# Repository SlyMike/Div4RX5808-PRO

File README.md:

# Div4RX5808-PRO
Arduino based 5.8GHz  Diversity Video receiver using 2x RX5808-PRO RX modules.

This project requires that you make 3 seperate PCB's. Two RX5808-PRO enabled video RX modules and a Diversity main board.
Boards and schematics are supplied for both the receivers and mainboard. 
Boards and schematics are in Eagle PCB format.

The RX modules will need to be assembled and programmed with the RX5808-PRO software (available on Github).
The diversity code for the Main board is available within this repository. After downloading, replace the .C file extension with .ino and upload.

The Main board and RX modules will require an Arduino Nano with an Atmega328.

The software portion of this project is not an adaptation of RX5808-PRO, it's function is to monitor 2x RSSI inputs from 2x RX5808-PRO enabled receivers and display the video feed from the receiver with the better signal. 
Video, audio and controls are switched simultaniously. LEDs indicate RSSI percentage (4 LEDs), active receiver (2 LEDs) and diversity mode (1 LED).

Holding the "Video" button during boot will allow for RSSI calibration as many RX5808 modules will have slightly different lower and upper limits.
The Div4RX5808-PRO diversity video receiver will assume that channel selection is correct and that nobody else is using the chosen channel.
The transmitter on the RC model should be set to the same channel as the receiver, the model should be powered down.

(1) Turn on Div4RX5808-PRO diversity video receiver in RSSI calibration mode (TX OFF). Amber led indicates LOW RSSI calculation. Press and release "Mode" button.
(2) Turn on transmitter. Second amber led indicates HIGH RSSI calculation. Press and release "Mode" button.
(3) Green LED indicates a good calibration, red a failure.

Auto calibration may not be necessary and if it is not initiated on power up (or fails for some reason), received RSSI values will be directly compared as if limits are equal on both modules.

Hold the "Mode" button during power up to enable serial debug output.

The code has been tested to a degree, it seems to work for me but there is always room for improvement.
I consider this project a work in progress, you may find bugs, spelling mistakes, missing component values, most of the source files were made in a rush or whilst I was doing something else.

I may address this in future but for most folk it should not be hard to build.

The point of this project was to create a decent micro controlled diversity receiver with better features than some of the crude homebrew solutions that I found on the net. I'm pretty sure I met my goal!

      FEATURES:
      
      *** AUTO RSSI CALIBRATION ***
      
      RX5808-PRO SUPPORT.
      
      LIVE VIDEO / SPECTRUM ANALYSER SWITCHING VIA PUSH BUTTON.
      SINGLE RX OR DIVERSITY MODES VIA PUSH BUTTON.
      SERIAL DEBUG MODE VIA PUSH BUTTON.
      TOTAL 6 PUSH BUTTONS FOR EASY OPERATION.
      SOFTWARE SWITCH DE-BOUNCING.
      
      MODE LED INDICATORS.
      RSSI LED INDICATORS.
      RX LED INDICATORS.
      
      VARIABLE RSSI SMOOTHING.
      VARIABLE RX SWITCHING RATE.
      VARIABLE RSSI HYSTERESIS.
      
      CHOICE OF VOLTAGE REFERENCE METHODS - CODE WILL WORK ON 3V3 AND 5V TARGETS.
      WELL COMMENTED CODE.

I hope you find this project helpful, maybe it's worth a coffee?

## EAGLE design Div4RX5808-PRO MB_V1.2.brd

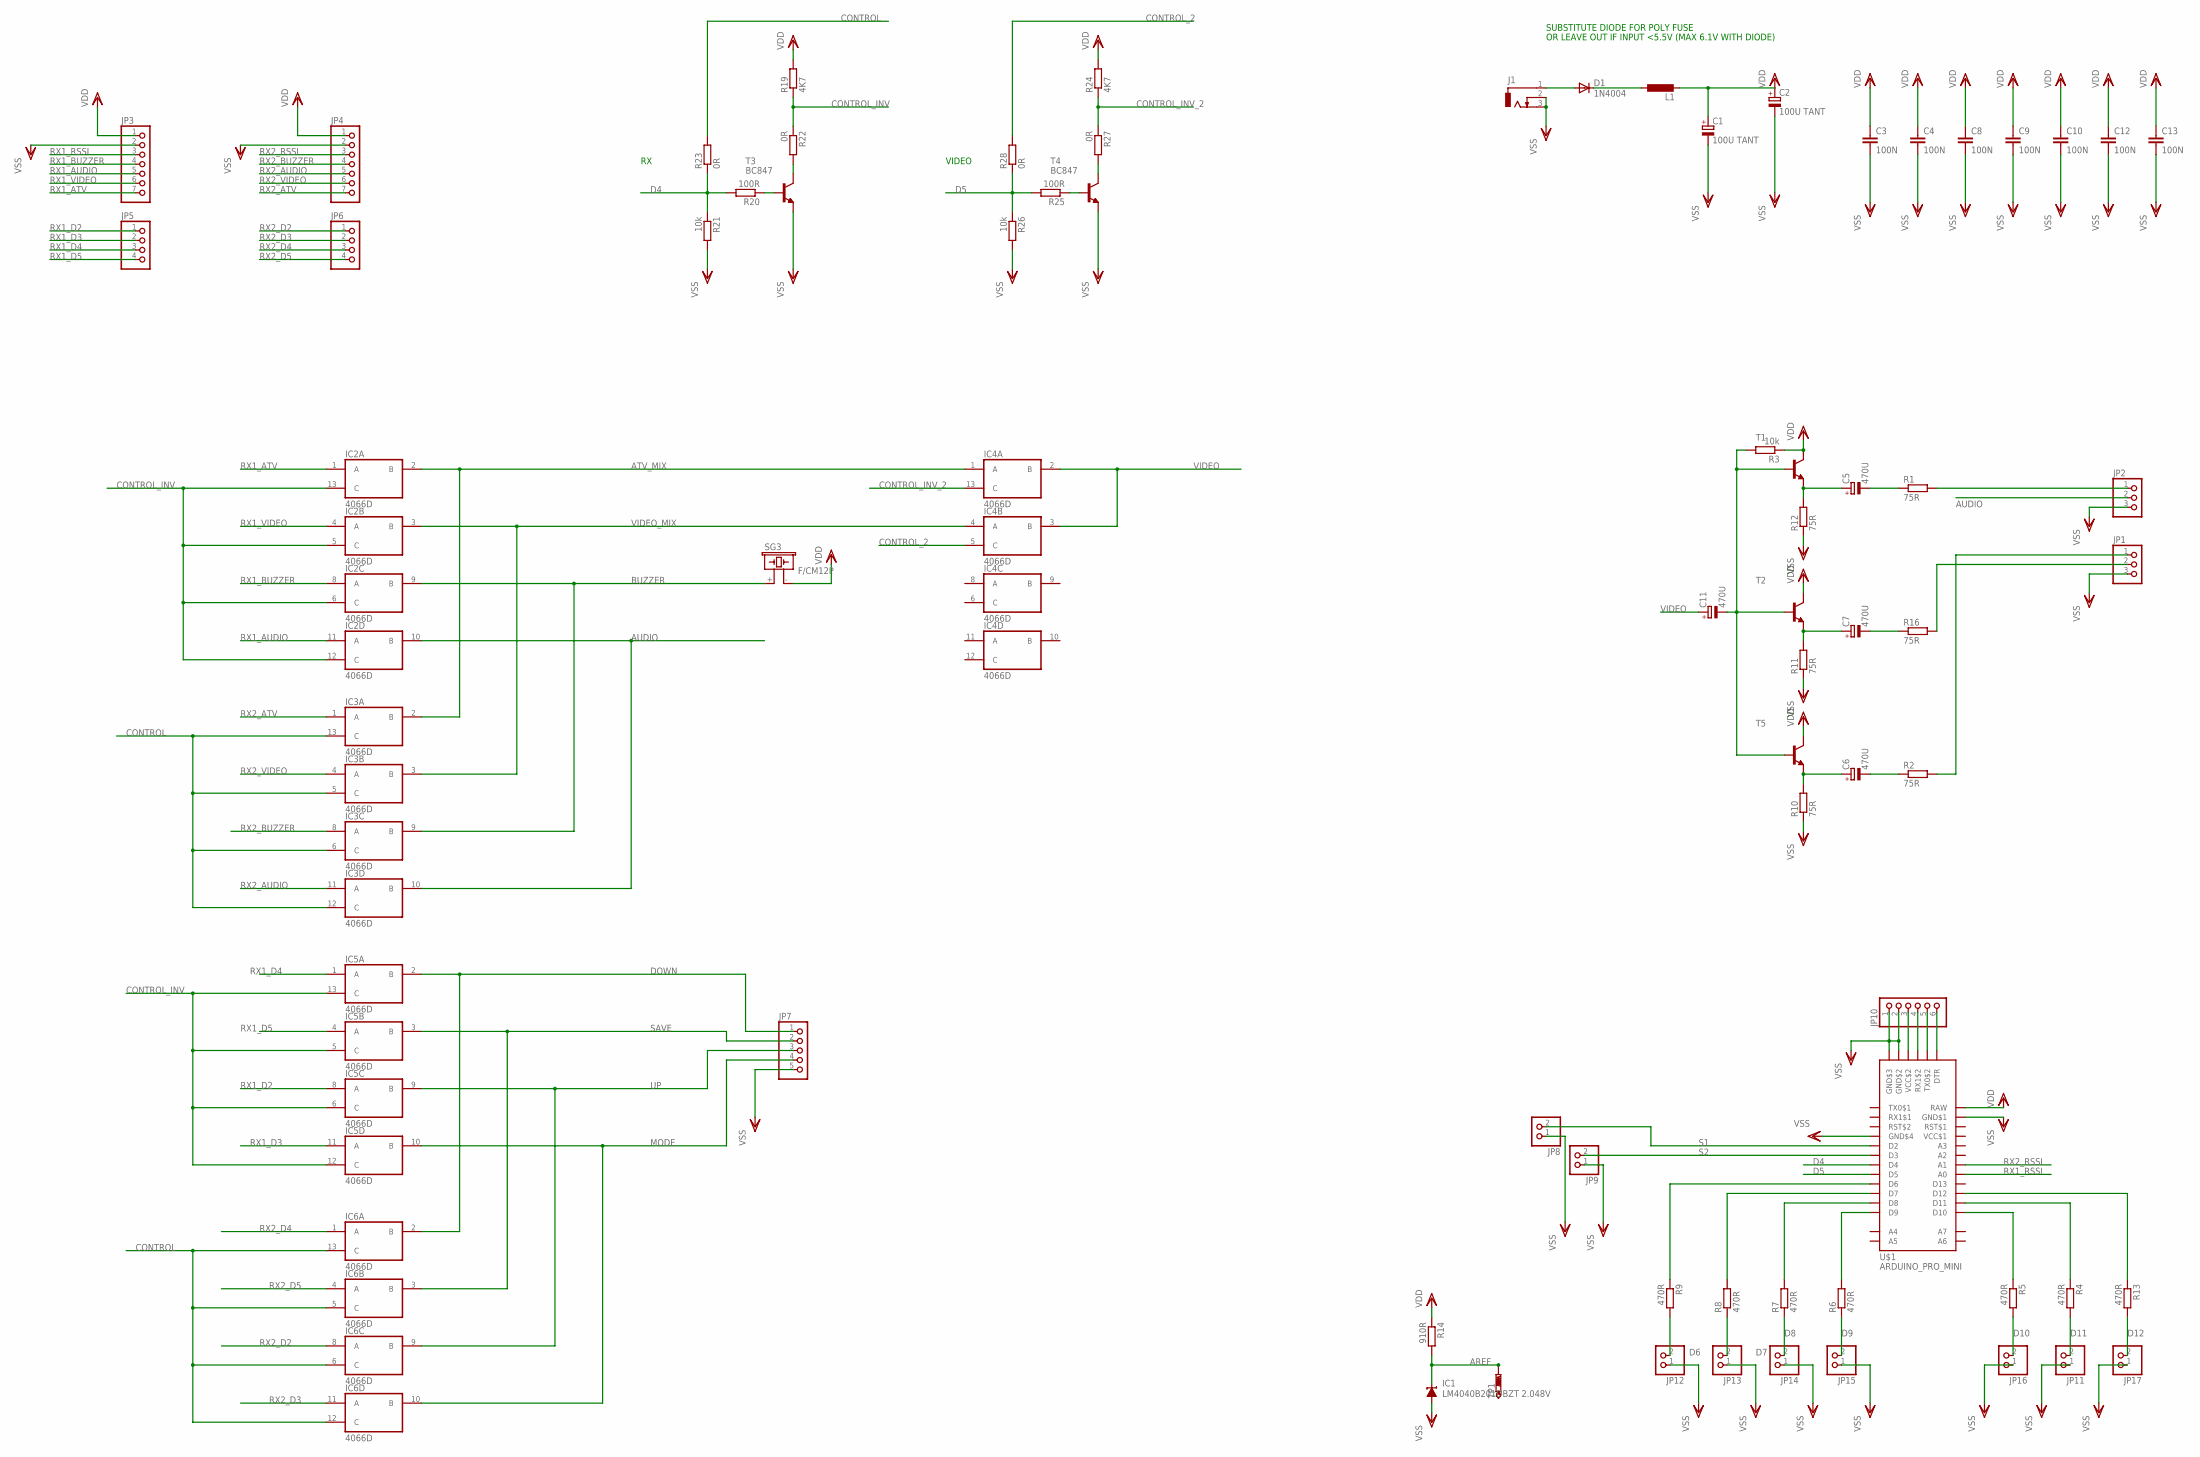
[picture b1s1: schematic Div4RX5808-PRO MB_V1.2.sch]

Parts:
C1, C2: 100U TANT; C/6032-28R
C3, C4, C8, C9, C10, C12, C13: 100N; C0603
C5, C6, C7, C11: 470U; E5-10,5
D1: 1N4004; DO41-10
IC1: LM4040B201DBZT 2.048V; DBZ_R-PDSO-G3
IC2, IC3, IC4, IC5, IC6: 4066D; SO14
J1: DCJ0303
JP1, JP2: PINHD-1X3; 1X03
JP3, JP4: PINHD-1X7; 1X07
JP5, JP6: PINHD-1X4; 1X04
JP7: PINHD-1X5; 1X05
JP8, JP9, JP11, JP12, JP13, JP14, JP15, JP16, JP17: PINHD-1X2; 1X02
JP10: PINHD-1X6; 1X06
L1: L-EU0207/7; 0207/7
R1, R2, R10, R11, R12, R16: 75R; M0805
R3, R21, R26: 10k; M0805
R4, R5, R6, R7, R8, R9, R13: 470R; R0603
R14: 910R; R0603
R19, R24: 4K7; M0805
R20, R25: 100R; M0805
R22, R23, R27, R28: 0R; M0805
SG3: F/CM12P
T1, T2, T5: MMBT2222ALT1-NPN-SOT23-BEC; SOT23-BEC
T3, T4: BC847; SOT23-BEC
TP1: PTR1TP20SQ; TP20SQ
U$1: ARDUINO_PRO_MINI

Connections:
AREF: IC1.1 (C), R14.2, TP1.TP
ATV_MIX: IC2.2 (B), IC3.2 (B), IC4.1 (A)
AUDIO: IC2.10 (B), IC3.10 (B), JP2.2
BUZZER: IC2.9 (B), IC3.9 (B), SG3.+ (1)
CONTROL: IC3.5 (C), IC3.6 (C), IC3.12 (C), IC3.13 (C), IC6.5 (C), IC6.6 (C), IC6.12 (C), IC6.13 (C), R23.2
CONTROL_2: IC4.5 (C), R28.2
CONTROL_INV: IC2.5 (C), IC2.6 (C), IC2.12 (C), IC2.13 (C), IC5.5 (C), IC5.6 (C), IC5.12 (C), IC5.13 (C), R19.1, R22.1
CONTROL_INV_2: IC4.13 (C), R24.1, R27.1
D4: R20.2, R21.1, R23.1, U$1.D4
D5: R25.2, R26.1, R28.1, U$1.D5
D6: JP12.2, R9.2
D7: JP13.2, R8.1
D8: JP14.2, R7.1
D9: JP15.2, R6.1
D10: JP16.2, R5.2
D11: JP11.2, R4.2
D12: JP17.2, R13.2
DOWN: IC5.2 (B), IC6.2 (B), JP7.1
MODE: IC5.10 (B), IC6.10 (B), JP7.4
unnamed: D1.C, L1.1
unnamed: D1.A, J1.1
unnamed: R13.1, U$1.D12
unnamed: C5.-, R1.1
unnamed: C6.-, R2.1
unnamed: JP2.1, R1.2
unnamed: C7.-, R16.1
unnamed: JP1.2, R16.2
unnamed: JP1.1, R2.2
unnamed: C5.+, R12.2, T1.E
unnamed: JP10.6, U$1.DTR
unnamed: JP10.5, U$1.TX0$2
unnamed: C7.+, R11.2, T2.E
unnamed: JP10.4, U$1.RX1$2
unnamed: JP10.3, U$1.VCC$2
unnamed: R25.1, T4.B
unnamed: C6.+, R10.2, T5.E
unnamed: R22.2, T3.C
unnamed: R20.1, T3.B
unnamed: R27.2, T4.C
unnamed: C11.-, R3.2, T1.B, T2.B, T5.B
unnamed: R9.1, U$1.D6
unnamed: R8.2, U$1.D7
unnamed: R6.2, U$1.D9
unnamed: R4.1, U$1.D11
unnamed: R5.1, U$1.D10
unnamed: R7.2, U$1.D8
RX1_ATV: IC2.1 (A), JP3.7
RX1_AUDIO: IC2.11 (A), JP3.5
RX1_BUZZER: IC2.8 (A), JP3.4
RX1_D2: IC5.8 (A), JP5.1
RX1_D3: IC5.11 (A), JP5.2
RX1_D4: IC5.1 (A), JP5.3
RX1_D5: IC5.4 (A), JP5.4
RX1_RSSI: JP3.3, U$1.A0
RX1_VIDEO: IC2.4 (A), JP3.6
RX2_ATV: IC3.1 (A), JP4.7
RX2_AUDIO: IC3.11 (A), JP4.5
RX2_BUZZER: IC3.8 (A), JP4.4
RX2_D2: IC6.8 (A), JP6.1
RX2_D3: IC6.11 (A), JP6.2
RX2_D4: IC6.1 (A), JP6.3
RX2_D5: IC6.4 (A), JP6.4
RX2_RSSI: JP4.3, U$1.A1
RX2_VIDEO: IC3.4 (A), JP4.6
S1: JP8.2, U$1.D2
S2: JP9.2, U$1.D3
SAVE: IC5.3 (B), IC6.3 (B), JP7.2
UP: IC5.9 (B), IC6.9 (B), JP7.3
VCC$1: U$1.VCC$1
VDD: C1.+, C2.+, C3.1, C4.1, C8.1, C9.1, C10.1, C12.1, C13.1, IC2.14 (VDD), IC3.14 (VDD), IC4.14 (VDD), IC5.14 (VDD), IC6.14 (VDD), JP3.1, JP4.1, L1.2, R3.1, R14.1, R19.2, R24.2, SG3.- (2), T1.C, T2.C, T5.C, U$1.RAW
VIDEO: C11.+, IC4.2 (B), IC4.3 (B)
VIDEO_MIX: IC2.3 (B), IC3.3 (B), IC4.4 (A)
VSS: C1.-, C2.-, C3.2, C4.2, C8.2, C9.2, C10.2, C12.2, C13.2, IC1.2 (A), IC2.7 (VSS), IC3.7 (VSS), IC4.7 (VSS), IC5.7 (VSS), IC6.7 (VSS), J1.2, J1.3, JP1.3, JP2.3, JP3.2, JP4.2, JP7.5, JP8.1, JP9.1, JP10.1, JP10.2, JP11.1, JP12.1, JP13.1, JP14.1, JP15.1, JP16.1, JP17.1, R10.1, R11.1, R12.1, R21.2, R26.2, T3.E, T4.E, U$1.GDN$1 (GND$1), U$1.GND$2, U$1.GND$3, U$1.GND$4

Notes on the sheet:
VIDEO
SUBSTITUTE DIODE FOR POLY FUSE
OR LEAVE OUT IF INPUT <5.5V (MAX 6.1V WITH DIODE)

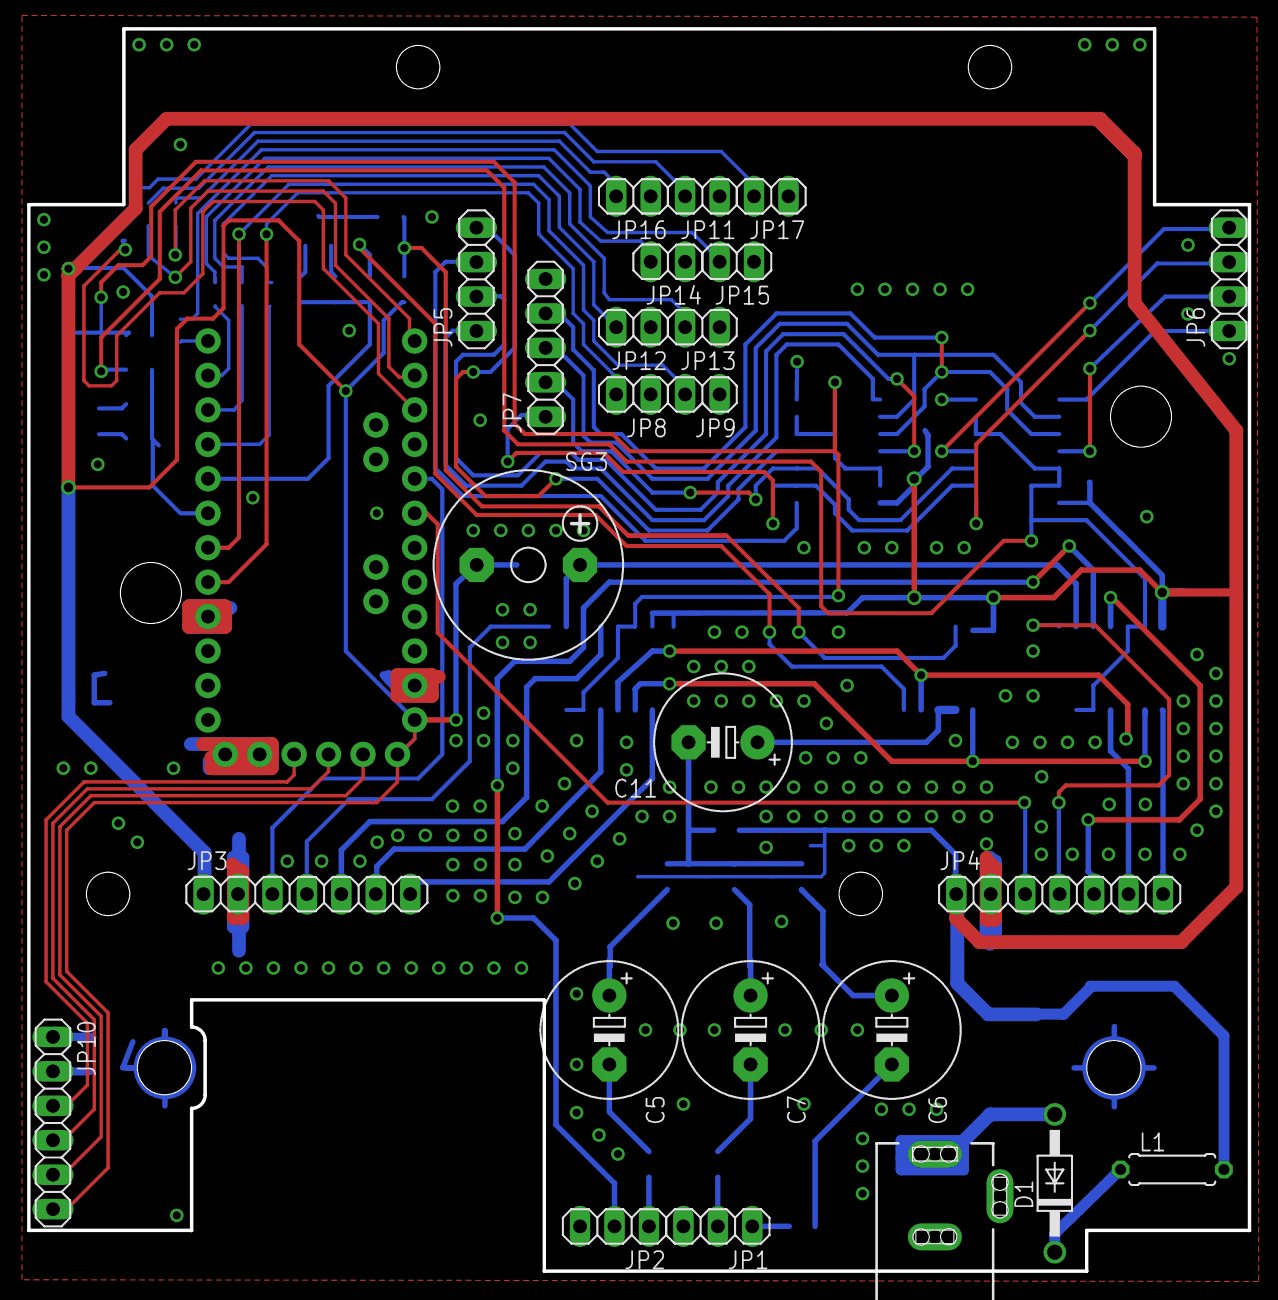
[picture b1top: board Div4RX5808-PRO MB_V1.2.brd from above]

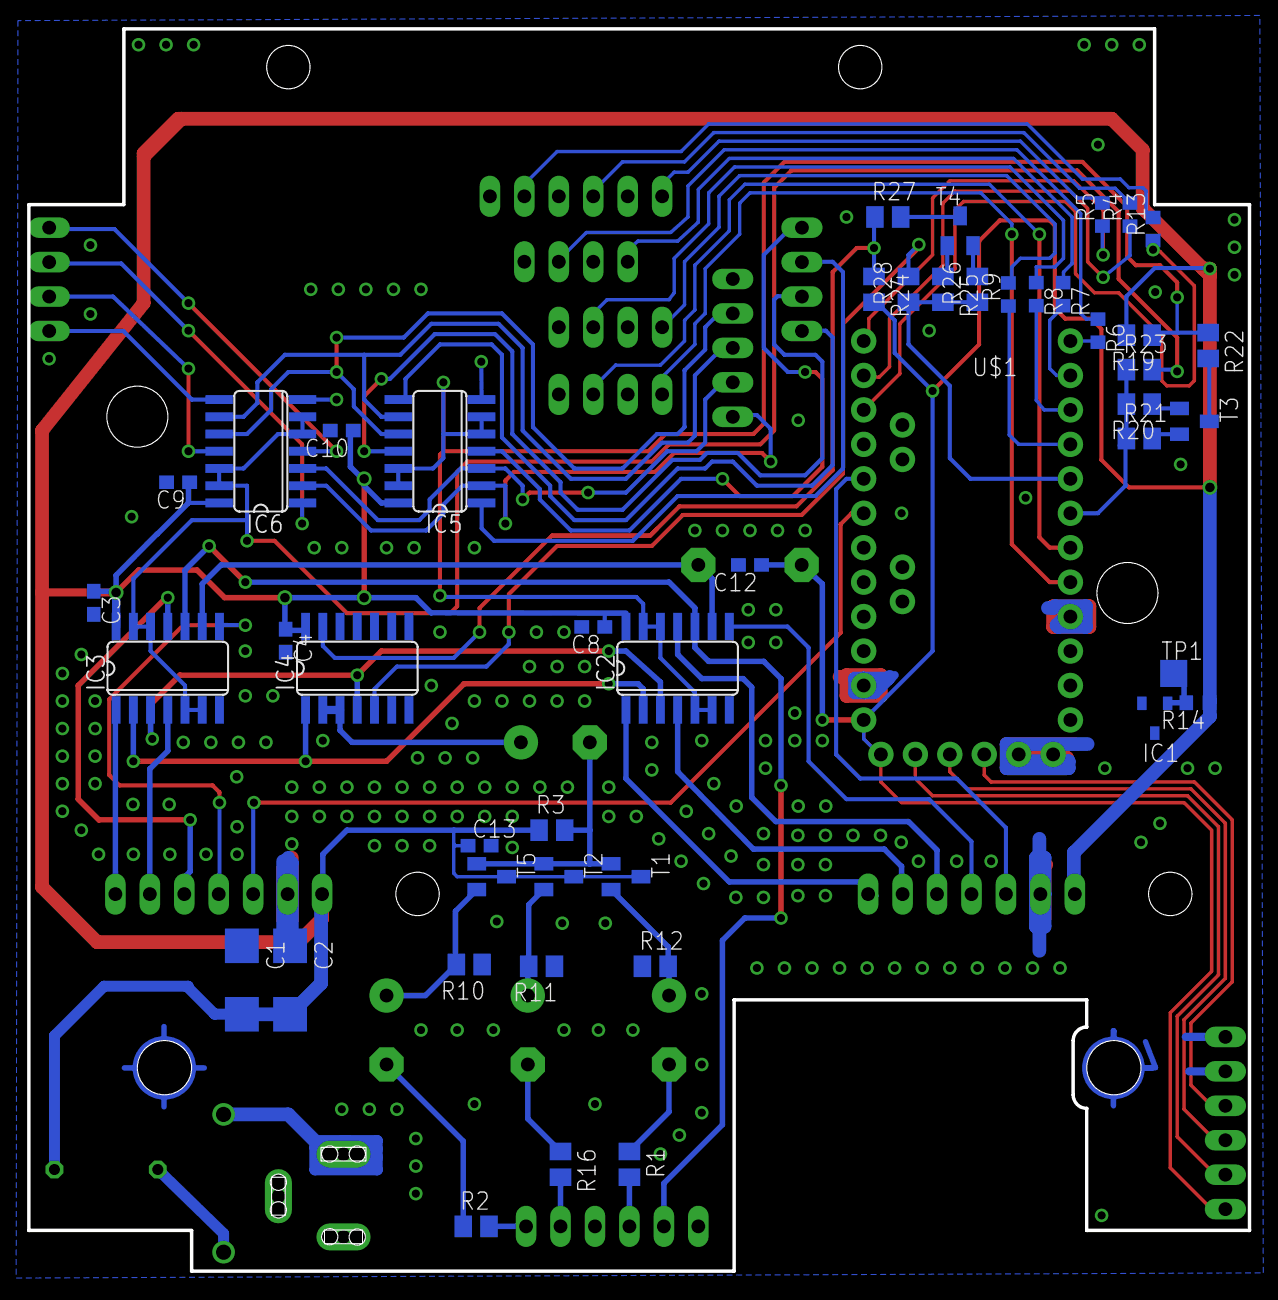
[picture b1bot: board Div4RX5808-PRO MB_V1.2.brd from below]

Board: 2 copper layers, 90.0 x 91.6 mm, 72 parts (47 on the bottom side), 72 nets.

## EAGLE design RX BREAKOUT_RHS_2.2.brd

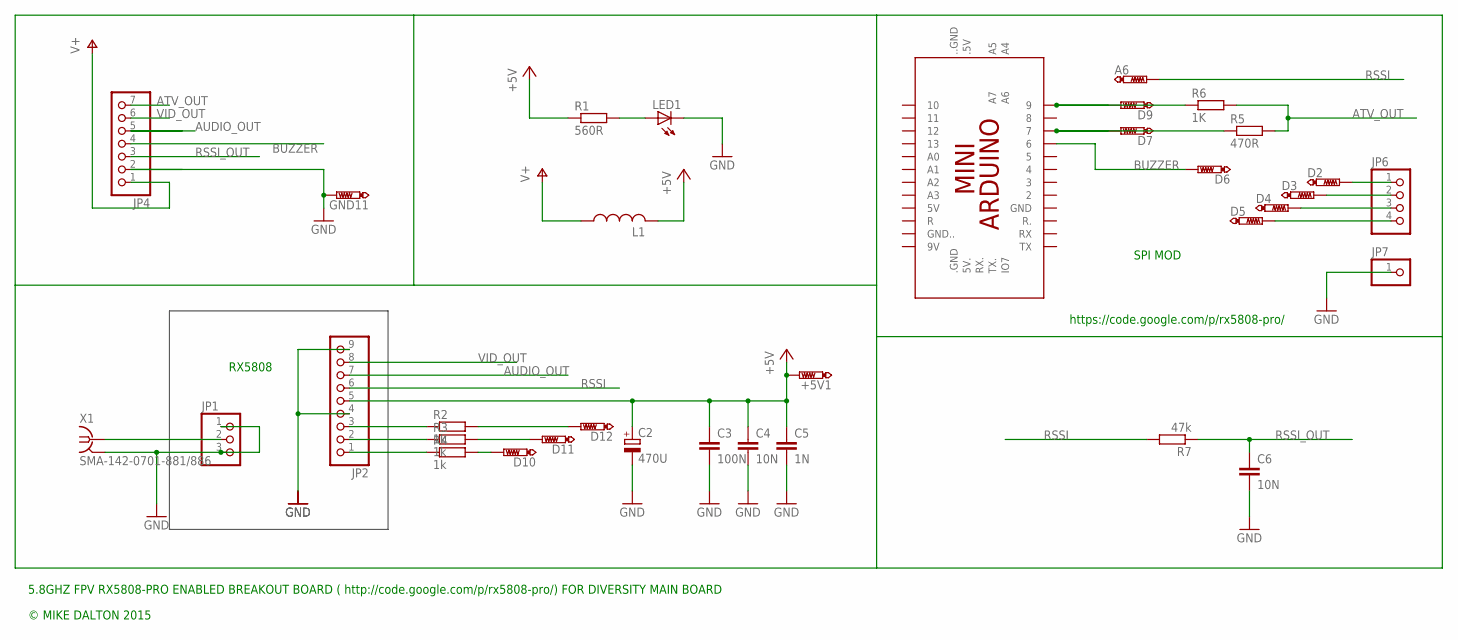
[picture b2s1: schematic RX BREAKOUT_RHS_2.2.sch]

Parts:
+5V1: PTR1TP16SQ; TP16SQ
A6: PTR1TP16SQ; TP16SQ
C2: 470U; E5-10,5
C3: 100N; C0603K
C4, C6: 10N; C0603K
C5: 1N; C0603K
D2, D3, D4, D5, D6, D7, D9, D10, D11, D12: PTR1TP16SQ; TP16SQ
GND11: PTR1TP16SQ; TP16SQ
JP1: PINHD-1X3; 1X03
JP2: PINHD-1X9; 1X09
JP4: PINHD-1X7; 1X07
JP6: PINHD-1X4; 1X04
JP7: PINHD-1X1; 1X01
L1: L-USL4532C; L4532M
LED1: LEDSMT1206; 1206
R1: 560R; R0603
R2, R3, R4: 1k; R0603
R5: 470R; R0603
R6: 1K; R0603
R7: 47k; R0603
X1: SMA-142-0701-881/886; J502-ND-142-0701-881/886

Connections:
ATV_OUT: JP4.7, R5.2, R6.2
AUDIO_OUT: JP2.7, JP4.5
BUZZER: D6.TP, JP4.4
D7: D7.TP, R5.1
D9: D9.TP, R6.1
GND: C2.-, C3.2, C4.2, C5.2, C6.2, GND11.TP, JP1.1, JP1.3, JP2.4, JP2.9, JP4.2, JP7.1, LED1.C, X1.G@1 (2), X1.G@2 (2), X1.G@3 (2), X1.G@4 (2)
unnamed: D12.TP, R2.2
unnamed: JP2.3, R2.1
unnamed: D11.TP, R3.2
unnamed: LED1.A, R1.2
unnamed: JP1.2, X1.1
unnamed: D10.TP, R4.2
unnamed: JP2.2, R3.1
unnamed: +5V1.TP, C2.+, C3.1, C4.1, C5.1, JP2.5, L1.2, R1.1
unnamed: JP2.1, R4.1
unnamed: D2.TP, JP6.1
unnamed: D3.TP, JP6.2
unnamed: D4.TP, JP6.3
unnamed: D5.TP, JP6.4
RSSI: A6.TP, JP2.6, R7.2
RSSI_OUT: C6.1, JP4.3, R7.1
V+: JP4.1, L1.1
VID_OUT: JP2.8, JP4.6

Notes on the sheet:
RX5808
SPI MOD
https://code.google.com/p/rx5808-pro/
© MIKE DALTON 2015
5.8GHZ FPV RX5808-PRO ENABLED BREAKOUT BOARD ( http://code.google.com/p/rx5808-pro/) FOR DIVERSITY MAIN BOARD

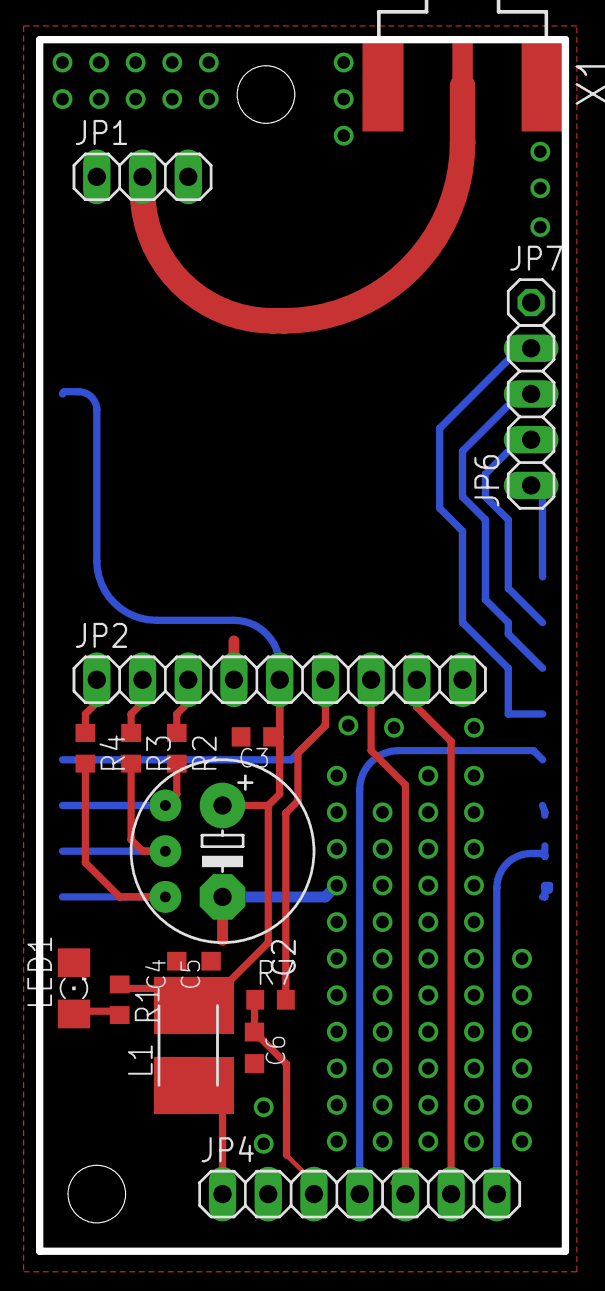
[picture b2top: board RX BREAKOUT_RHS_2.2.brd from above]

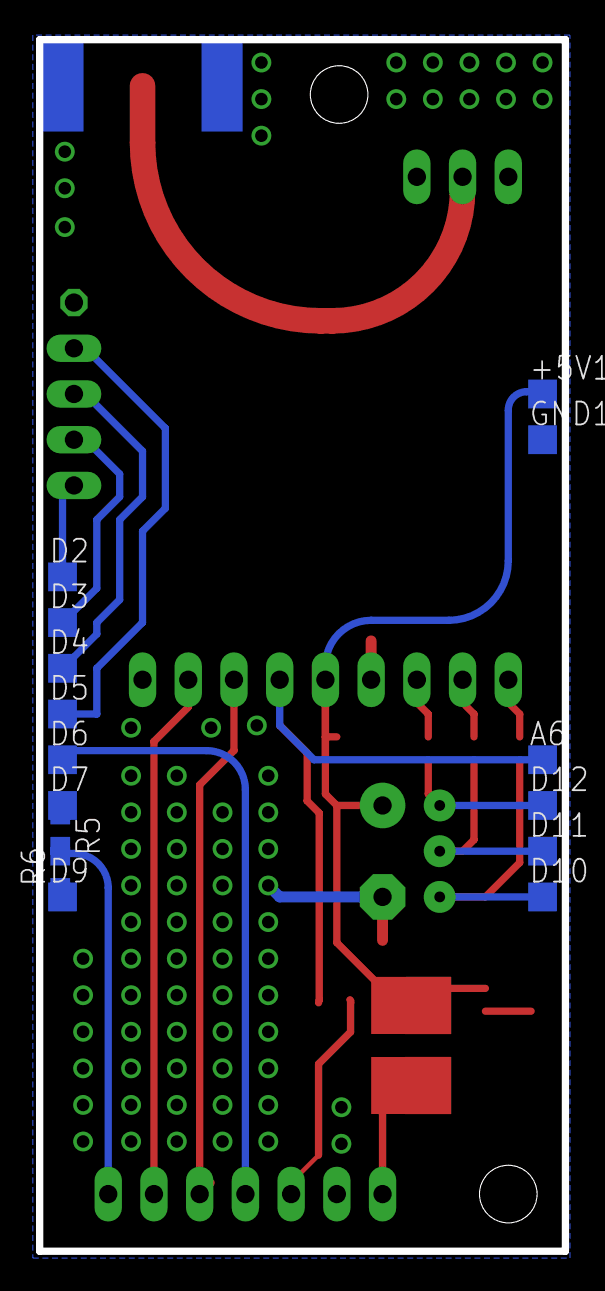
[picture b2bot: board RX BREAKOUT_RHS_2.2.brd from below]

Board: 2 copper layers, 29.2 x 67.3 mm, 33 parts (15 on the bottom side), 23 nets.

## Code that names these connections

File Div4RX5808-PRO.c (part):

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
 Physical pins used:

 A0      RSSI1_ADC_PIN           ANALOGUE INPUT    left channel RSSI input (RX1, 0.5V-1.2V).
 A1      RSSI2_ADC_PIN           ANALOGUE INPUT    right channel RSSI input (RX2, 0.5V-1.2V).
 A2      N/A                     N/A               N/A
 A3      N/A                     N/A               N/A
 A4      N/A                     N/A               N/A
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 D1      SERIAL                  RX                Serial connection
 D2      MODE_SWITCH             INPUT PULLUP      Switch 1, Mode select between left channel, right channel and diversity using RSSI. (ENTERS DEBUG MODE AT POWER UP)
 D3      VIDEO_SWITCH            INPUT PULLUP      Switch 2, selects between live video output from selected receiver and ATV (spectrum analyser) output from RX8505-PRO board.
 D4      RX_CONTROL_PIN          OUTPUT            Pin to control switching between receiver 1 and 2, default LOW - RX1.
 D5      VIDEO_CONTROL_PIN       OUTPUT            Pin to control switching between live video and ATV. (ATV = Arduino TV out - SPECTRUM ANALYSER)
 D6      LED_RX_1                OUTPUT            LED for RX1 radio.
 D7      LED_RX_2                OUTPUT            LED for RX2 radio.
 D8      LED_025_P               OUTPUT            RED LED to display RSSI between 0%-25%.
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

/* Physical pin assignments. */
#define RSSI1_ADC_PIN A0                                /* ADC connected to reciever 1 RSSI output pin. */
#define RSSI2_ADC_PIN A1                                /* ADC connected to reciever 2 RSSI output pin. */
#define MODE_SWITCH 2                                   /* Press this button to switch between available RX modes. */
#define VIDEO_SWITCH 3                                  /* Press this button to switch between live video and spectrum analyser. */
#define RX_CONTROL_PIN 4                                /* Toggled by software to select RX unit. */
#define VIDEO_CONTROL_PIN 5                             /* Toggled by software to select between live video and spectrum analyser. */

/* LEDs. */
#define LED_RX_1 6                                      /* RX1 status LED. */
#define LED_RX_2 7                                      /* RX2 status LED. */
#define LED_025_P 8                                     /* RSSI 0%-25% status LED. */
#define LED_050_P 9                                     /* RSSI 26%-50% status LED. */
#define LED_075_P 10                                    /* RSSI 51%-75% status LED. */
#define LED_100_P 11                                    /* RSSI 76%-100% status LED. */
#define LED_DIVERSITY 12                                /* Diversity active indicator LED. */
#define LED_HEARTBEAT 13                                /* Heartbeat, indicates loop speed, for initial debug. */

/* Delays. */
#define ADC_WARMUP_DELAY 1                              /* Time to let ADCs settle. Default 1. */
#define BUTTON_DEBOUNCE_MILLIS 250                      /* Push button debounce value. Default 250. */
#define DIVERSITY_INTERVAL_MILLIS 2000                  /* Minimum allowable time before video pin toggles. Default 500. */
#define CALIB_STAB_CYCLES 1000                          /* Calibration stabilization cycles. Give pleanty of cycles for averages to become stable figures. Default 1000. */
#define CALIB_TIMEOUT_MILLIS 30000                      /* Give up calibrating after X seconds. Default 30000. */
#define ONE_TIME_WARMUP_DELAY 5000                      /* A one time delay to allow voltages to stabilize on the TX and RC model during Auto Calibration. Default 5000. */
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#define COMPILER __VERSION__                            /* Version info. */

/* RSSI. */
#define MAX_AVERAGE_READINGS 10                         /* Smoothing value for RSSI averages. Default 10. */
#define RSSI_HYSTERESIS 1                               /* This hysteresis value is a % of the calculated RSSI value. Default 1. */

                                                        /* RSSI voltage range is between 0.5v and 1.1v for most rx5808 modules. */
unsigned int RSSI1Min = 512;                            /* Default 512. */
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/* Voltage. */
float ADC_MAX = 1024.0;                                 /* Max ADC value. */
float RSSIARef = 1.1;                                   /* Voltage of selected analogue reference. (see below, setup) */
float RSSI1Volts = 0;                                   /* Calculated voltage on RSSI pin. */
float RSSI2Volts = 0;                                   /* Calculated voltage on RSSI pin. */

/* Buttons. */
int VideoControlPinState = LOW;                         /* The current state of the output pin. */
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    pinMode(RSSI2_ADC_PIN, INPUT);

    pinMode(MODE_SWITCH, INPUT_PULLUP);                 /* Hold during power up to enter debug mode. */
    pinMode(VIDEO_SWITCH, INPUT_PULLUP);                /* Hold during power up to enter auto RSSI calibration mode mode. */
                                                        /* Both buttons can be held simultaneously. */
    pinMode(RX_CONTROL_PIN, OUTPUT);
    pinMode(VIDEO_CONTROL_PIN, OUTPUT);
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    }

    digitalWrite(RX_CONTROL_PIN, LOW);        /* Default RX module on start-up. */
    digitalWrite(VIDEO_CONTROL_PIN, LOW);     /* Default screen (live video / spectrum analyser) on start-up. */

    digitalWrite(LED_025_P, HIGH);            /* flash some LEDs. */
    delay(150);
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  /******************************************************************************
    RSSI CALCULATIONS

    RSSI figures need averaging, turning into a percentage and clipping.
    ******************************************************************************/


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        }
    }

    /* Calculate voltages of RSSI pins. */
    RSSI1Volts = (RSSI1InputPinValue / ADC_MAX) * RSSIARef;
    RSSI2Volts = (RSSI2InputPinValue / ADC_MAX) * RSSIARef;

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        Serial.print("  MODE =");                   /* Current mode (3 IS DIVERSITY) */
        Serial.print(ModeSwitchCounter);

        Serial.print("  RX =");                     /* state of video RX selector pin. */
        Serial.println(RxControlPinState);

        Serial.print("  Elapsed ");               /* Time since RX modules were toggled. */
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
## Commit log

2016-11-23 Create RX5808-PRO

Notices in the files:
Div4RX5808-PRO MB_V1.2.brd:
V1.2  © MIKE DALTON 2015
Div4RX5808-PRO MB_V1.2.sch:
V1.0 © MIKE DALTON 2015
